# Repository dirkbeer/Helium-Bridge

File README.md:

### Helium Bridge

Helium Bridge is an Arduino application and printed circuit board (PCB) for ESP32 devices. It bridges data packets from sensors transmitting in the ISM bands (industrial, scientific, and medical) to LoRaWAN.

With a Helium Bridge device connecting to the Helium network,

* Off-the-shelf consumer and commercial sensors and IoT devices can be connected to the internet
* Data can be used for environmental modeling, weather dashboards, home automation, etc.
* Off-grid deployment simple since this is a compact, low power, inexpensive device 
* Many sensor devices can be relayed, and the code can be easily extended support over 100+ more
  
The Helium Bridge software and PCB design was sponsored by an innovation grant from the [Helium Foundation](https://www.helium.foundation/) to be made available open source. This work is freely available for use under its [MIT License](https://github.com/dirkbeer/Helium-Bridge/blob/main/LICENSE), copyright (c) 2023 Dirk Beer and [Gristle King, Inc](https://gristleking.com/). 

The Arduino code builds on these outstanding projects:

* [LMIC-node](https://github.com/lnlp/LMIC-node), an example LoRaWAN application for a node for The Things Network that helps get your node up and running quickly.
* [rtl_433_ESP](https://github.com/NorthernMan54/rtl_433_ESP), an Arduino library for use on ESP32 boards with a CC1101 transceiver or SX127X Transceivers with the device decoders from the rtl_433 package.
* [rtl_433](https://github.com/merbanan/rtl_433), which (despite the name) is a generic data receiver, mainly for the 433.92 MHz, 868 MHz (SRD), 315 MHz, 345 MHz, and 915 MHz ISM bands.

A version of this project with code specifically for the bridging the Ecowitt/FineOffset WS-80 Weather station to Helium, which includes some additional features and data handling for that device, is available at [Helium_Bridge_WS80](https://github.com/dirkbeer/Helium_Bridge_WS80). The PCB design is the same for both projects.

## Application
* Currently supports these 4 sensor devices (easily extended to more sensors on demand)
  * Ecowitt/Fine Offset WS-80 weather station
  * Ecowitt/Fine Offset WH-45 indoor air quality monitor
  * Acurite Tower temperature and humidity sensors
  * Springfield Soil moisture sensors
        
## Helium Bridge Device
* The bridge device can be built using our PCB board design and these components:
  * LILYGO® TTGO LoRa32 V2.1_1.6 board [link](https://www.lilygo.cc/products/lora3)
  * CC1101 RF Tranceiver Module "CC1101 868MHz" (green, squarish, no pins) [link](https://www.ebay.com/itm/311955775989)
  * 5V Polysilicon Solar Panel like this (don't use 6V panels, they may damage the Lilygo board) [link](https://www.amazon.com/gp/product/B0831CMJB9)
  * 18650 3.7V rechargeable battery
    
## Getting started
# Build a Helium Bridge device
1. Have the PCB printed: 
  * Locate the Gerber file: `Helium-Bridge/pcb/LoRaWan_Bridge_18650_CC1101SMD-Gerber.zip`
  * Order a PCB from an online service using the Gerber zip file. We used OSH Park.
  * Order a solder mask from an online services. We used OSH Stencils. When you upload the Gerber zip file there, use the layer `lorawan_bridge_18650_cc1101smd_f_paste.gbr` for the stencil.
2. In addition to the items listed above, you will need:
  * Solder paste and a method to reflow solder surface mount devices (SMDs). We used and highly recommend a DIY reflow oven like this: [link](https://whizoo.com/pages/buildguide).
  * 2.54mm pitch male and female straight single row pin headers for the Lilygo board, like the ones included in this kit [link](https://www.amazon.com/gp/product/B07CK3RCKS). You could also solder the board directly to the PCB, but it's very hard to unsolder if you run into problems.
  * A 5-Pin Micro USB Type B Male Connector for the solar panel [link](https://www.amazon.com/gp/product/B014GMP4E4)
  * An 18650 battery holder with through pins [link](https://www.digikey.com/short/39pht8dp)
  * A battery connector pigtail for connecting the Lilygo board battery input to the PCB
  * A 433MHz or 915MHz antenna with a U.FL connection
  * An SMD U.FL connector for the CC1101 antenna, like this [link](https://a.co/d/ePDIYed)
3. Use the solder mask to apply solder paste the the CC1101 and UF.L pads on the PCB, carefully place the CC1101 module and UF.L connector, and bake in the reflow oven at the temperature specified for your solder paste.
4. Once the PCB is cool, use a multimeter to test for shorts between adjacent pads of the CC1101 module and between the U.FL center pin and ground, and for good connections from pads to the module.
5. Solder the female pin headers, the battery holder, and the battery pigtail to the PCB. Pay attention to the polarity of the battery holder and pigtail.
6. Plug in the Lilygo board. To avoid damage to the devices, before you power it up, be sure to connect antennas to both the CC1101 U.FL connection and the Lilygo LoRa antenna connection.
7. Initial testing is best done without the battery or solar panel. Watch the polarity on the battery!
8. To use a solar panel, solder it to a 5-pin Micro-USB connector and plug it in to the Lilygo board.

# Run the Helium Bridge software
1. Set up a new Device on a Helium or Chirpstack Console. Edit `keyfiles/lorawan-keys_example.h` with your keys and save it as `keyfiles/lorawan-keys.h`
2. Configure the PlatformIO project. In the `platformio.ini` file, under `[env:ttgo_lora32_v21_rtl433_cc1101]` `build flags =`, specify
  * `'-DOOK_MODULATION=true' '-DRF_MODULE_FREQUENCY=433.92'` for 433MHz devices like the Acurite
  * `'-DOOK_MODULATION=false' '-DRF_MODULE_FREQUENCY=915.00'` for 915MHz devices like the Fine Offset devices
3. Upload and Monitor All using PlatformIO.
  * If LoRaWAN is working correctly, you should see the device sucessfully joining on the Helium or Chirpstack Console.
  * If the sensor decoding is working correctly, and you have one of the supported sensors up and running nearby, you should see JSON sensor data in the PlatformIO terminal
4. Use our script as the decoder Function on the Helium Console or JavaScript Codec on the Chripstack Console (it should work on both without modification)
  * Copy the content of `decoder.js` as the custom script. On Helium console, you can test the script with this example sensor data: `de7044af0a81cc`. You should see temperature and humidity. Save.
  * Connect the Function to the Device (Helium) or create an Application using the Device profile (Chripstack)
  * If everything is working, you should see data packets received in the Console, and decoded data in the Console debugger 

## Using the device
1. If desired, switch between 433MHz and 915MHz reception by sending a Downlink to the Device
  * Downlink settings should be FPort: _100_
  * On Helium Console, use payload type: _Text_. For 433MHz, send a `4`, for 915MHz, send a `9`
  * On Chirpstack Console, use payload type: _Hex_. For 433MHz, send a `34`, for 915MHz, send a `39`
2. You will have to wait for an uplink to occur, and *it may take several tries* for the downlink to be received and acted on by the bridge.
  * A limitation of LoRaWAN Class A devices like this one is that they can only receive a downlink if they have autonomously sent an uplink. You can make sure that uplinks happen periodically using `DO_WORK_INTERVAL_SECONDS` in `platformio.ini`. This is a heartbeat interval to ensure you can get a downlink command to the device even it it's not receiving & bridging any sensor packets.
  * When you are successful, the downlink will restart the device and will see JOIN requests in Console. If there are supported sensors nearby on the frequency you've switched to, you will see their data come in.

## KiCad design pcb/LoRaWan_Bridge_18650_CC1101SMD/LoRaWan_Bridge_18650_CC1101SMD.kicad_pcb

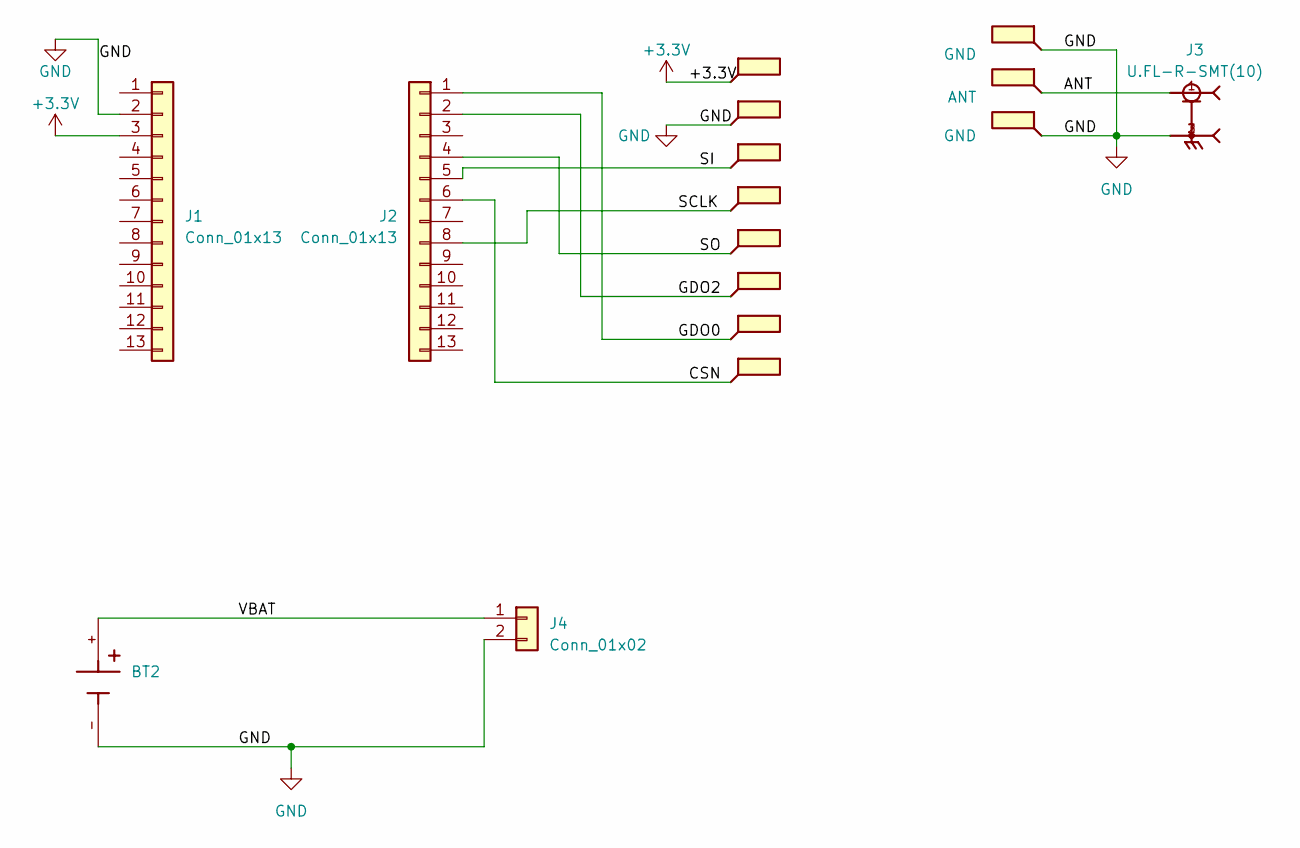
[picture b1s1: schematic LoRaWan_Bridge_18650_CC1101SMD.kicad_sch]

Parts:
BT2: BK-18650-PC2; BAT_BK-18650-PC2; PARTREV F
J1, J2: Conn_01x13; PinSocket_1x13_P2.54mm_Vertical
J3: U.FL-R-SMT(10); HRS_U.FL-R-SMT(10)
J4: Conn_01x02; PinSocket_1x02_P2.54mm_Vertical
P10, P12: GND; TestPoint_Pad_2.0x2.0mm
P11: ANT; TestPoint_Pad_2.0x2.0mm
TP1: VCC; TestPoint_Pad_1.2x2.0mm
TP2: GND; TestPoint_Pad_1.2x2.0mm
TP3: SI; TestPoint_Pad_1.2x2.0mm
TP4: SCLK; TestPoint_Pad_1.2x2.0mm
TP5: SO; TestPoint_Pad_1.2x2.0mm
TP6: GDO2; TestPoint_Pad_1.2x2.0mm
TP7: GDO0; TestPoint_Pad_1.2x2.0mm
TP8: CSN; TestPoint_Pad_1.2x2.0mm

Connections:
+3.3V: J1.3, TP1.1
/ANT: J3.1, P11.1
/CSN: J2.6, TP8.1
/GDO0: J2.1, TP7.1
/GDO2: J2.2, TP6.1
/SCLK: J2.8, TP4.1
/SI: J2.5, TP3.1
/SO: J2.4, TP5.1
/VBAT: BT2.+, J4.1
GND: BT2.-, J1.2, J3.2, J3.3, J4.2, P10.1, P12.1, TP2.1

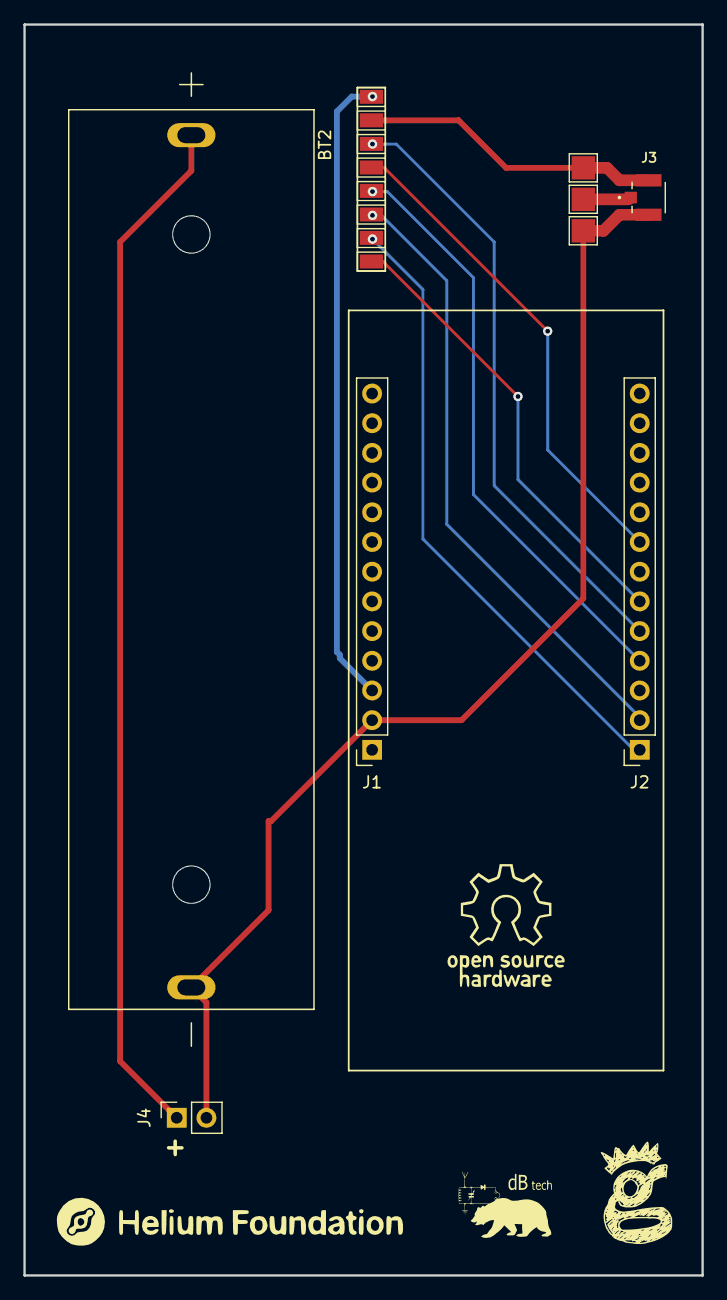
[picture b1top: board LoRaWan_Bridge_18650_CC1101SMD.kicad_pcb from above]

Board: 2 copper layers, 58.0 x 107.0 mm, 16 parts (0 on the bottom side), 10 nets.

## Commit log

2023-10-02 Updated decoder for chirpstack, but still not working
2023-10-02 Added heartbeat uplink /5minutes to ensure downlink capability
2023-10-06 springfield decoder fix
2023-10-09 downlink & mode switch debugging
2023-10-15 Add Gerber
2023-10-15 fix gerber name
2023-10-15 add drill files to gerber
